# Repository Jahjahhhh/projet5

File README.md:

# Standing desk projet

```/projet5/table-2/```: KiCAD files<br>
```/projet/arduino/projet5```: Arduino files

### Hardware
- 2x 12VDC Linear Actuators (12")
- ESP32 (To access the web and gather info for date, time, weather)
- Dual H-Bridge motor driver (each linear actuator pulls 5 A continuous)
- LED strip (5V Adressable LEDs)
- USB charging hub (2x USB-A & 1x USB-C)
- Ultrasonic sensor to detect when you go from standing to sitting
- MPU6050 (3 axis gyro and accelerometer) to measure the flatness of the table (in case the linear actuators are out of sync)
- 4 Debounced push buttons
- 1 SPDT toggle switch to control linear actuators (ON - OFF - ON)
- 1.8" OLED SPI display

### Schematic

<br>

### PCB

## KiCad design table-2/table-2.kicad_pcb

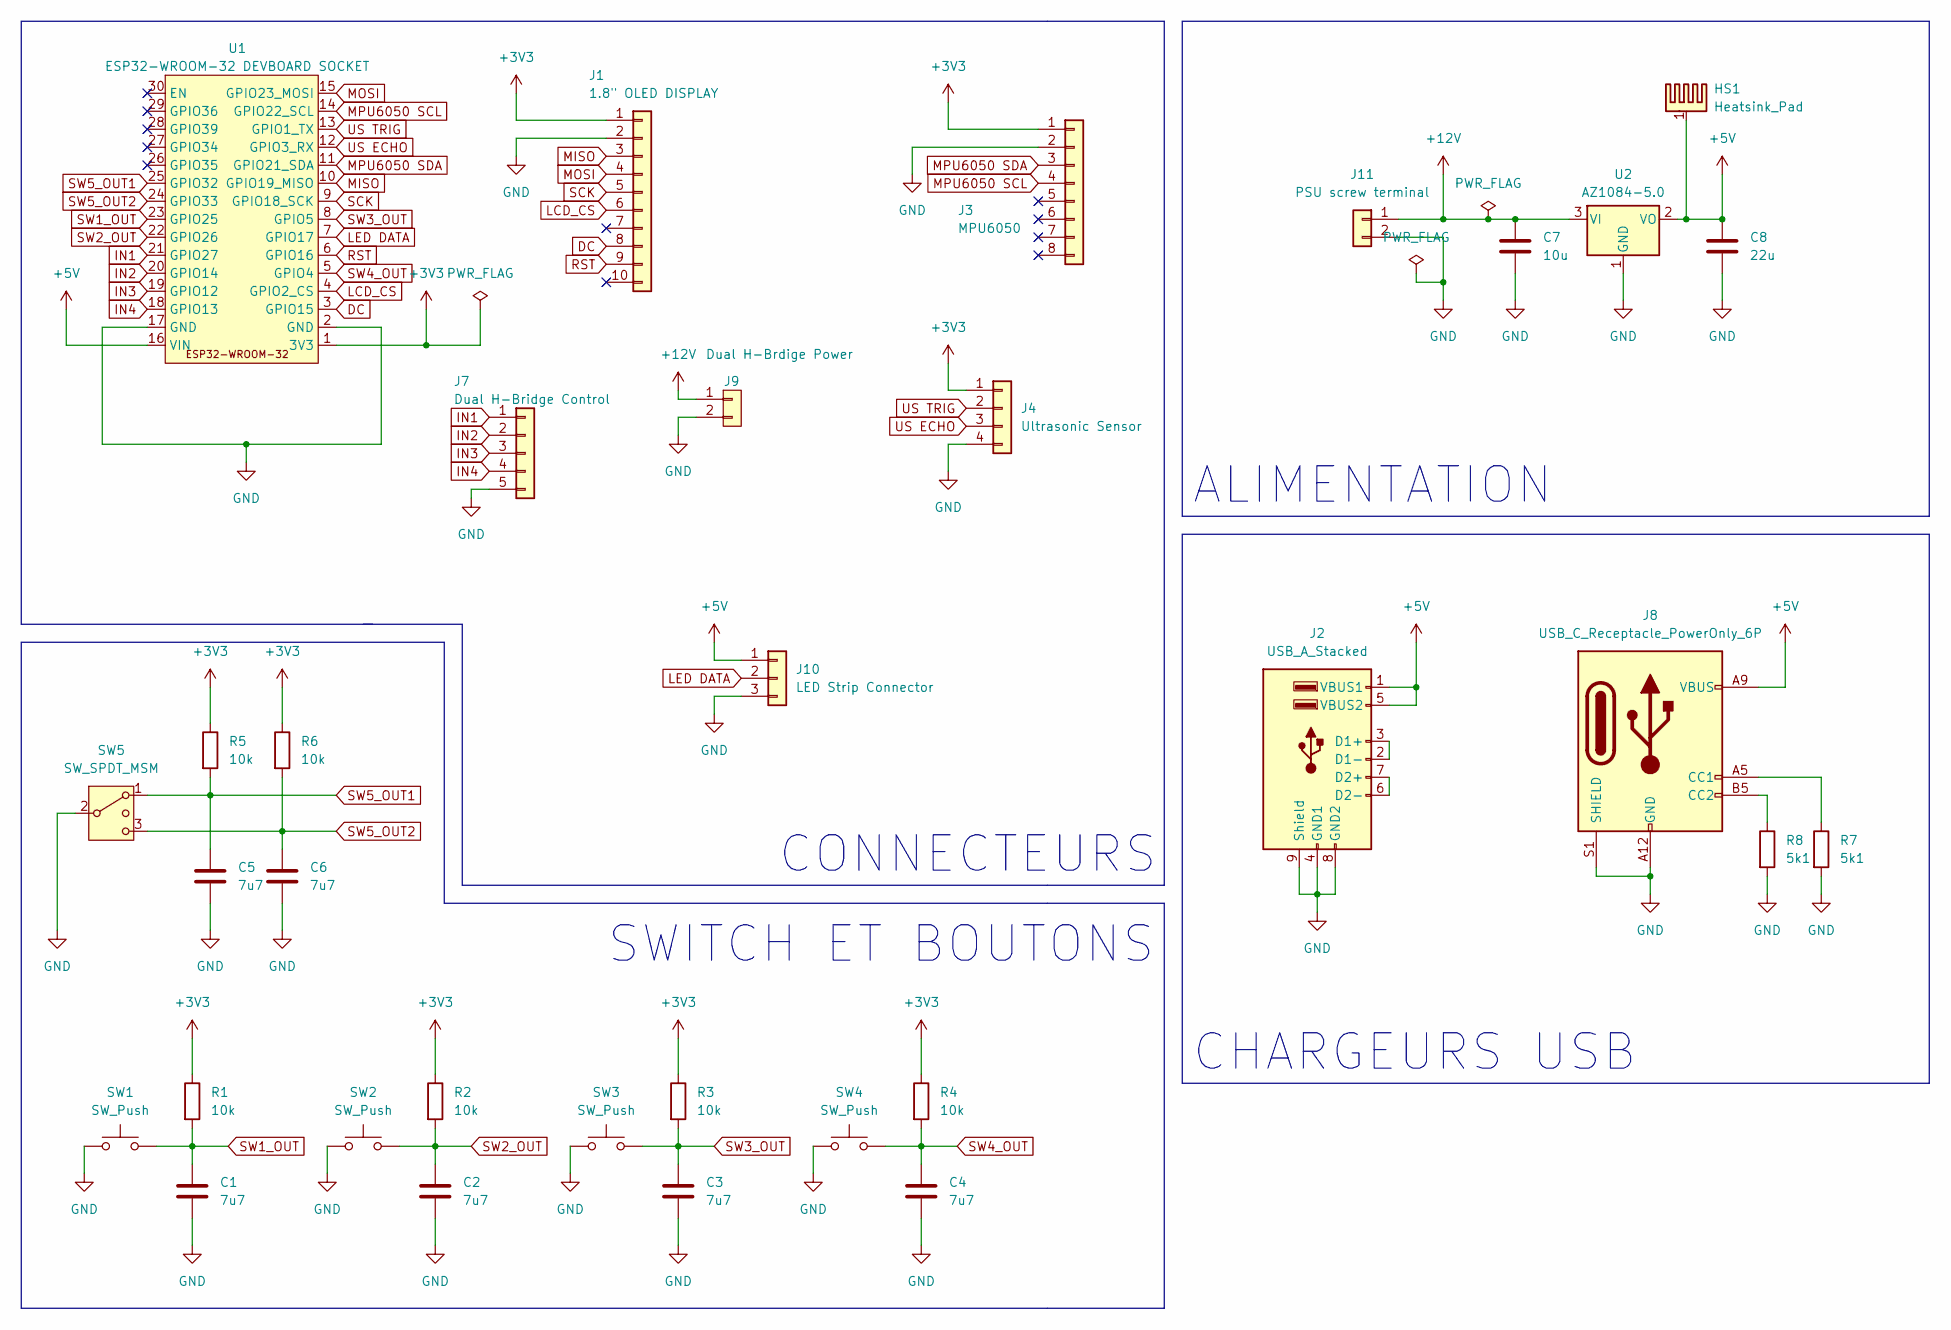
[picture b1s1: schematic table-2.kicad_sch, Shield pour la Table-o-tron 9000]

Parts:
C1, C2, C3, C4, C5, C6: 7u7; C_0805_2012Metric_Pad1.18x1.45mm_HandSolder
C7: 10u; C_0805_2012Metric_Pad1.18x1.45mm_HandSolder
C8: 22u; C_0805_2012Metric_Pad1.18x1.45mm_HandSolder
HS1: Heatsink_Pad; HEATSINK_573100D00000G
J1: 1.8" OLED DISPLAY; PinHeader_1x10_P2.54mm_Vertical
J2: USB_A_Stacked; USB_A_CUI_UJ2-ADH-TH_Horizontal_Stacked
J3: MPU6050; PinHeader_1x08_P2.54mm_Vertical
J4: Ultrasonic Sensor; PinHeader_1x04_P2.54mm_Vertical
J7: Dual H-Bridge Control; PinHeader_1x05_P2.54mm_Vertical
J8: USB_C_Receptacle_PowerOnly_6P; USB_C_Receptacle_GCT_USB4125-xx-x-0190_6P_TopMnt_Horizontal
J9: Dual H-Brdige Power; TerminalBlock_Wuerth_691311400102_P7.62mm; Manufacturer Part Number 0530480260
J10: LED Strip Connector; PinHeader_1x03_P2.54mm_Vertical
J11: PSU screw terminal; TerminalBlock_Wuerth_691311400102_P7.62mm
R1, R2, R3, R4, R5, R6: 10k; R_0805_2012Metric_Pad1.20x1.40mm_HandSolder
R7, R8: 5k1; R_0805_2012Metric_Pad1.20x1.40mm_HandSolder
SW1, SW2, SW3, SW4: SW_Push; Tactile_90_TE
SW5: SW_SPDT_MSM; BST13T1AVR
U1: ESP32-WROOM-32 DEVBOARD SOCKET; ESP32_WROOM_32
U2: AZ1084-5.0; AZ1084CD-5.0TRG1

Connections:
+3V3: J1.1, J3.1, J4.1, R1.1, R2.1, R3.1, R4.1, R5.1, R6.1, U1.1 (3V3)
+5V: C8.1, HS1.1, J2.1 (VBUS1), J2.5 (VBUS2), J8.A9 (VBUS), J8.B9 (VBUS), J10.1, U1.16 (VIN), U2.2 (VO)
+12V: C7.1, J9.1, J11.1, U2.3 (VI)
DC: J1.8, U1.3 (GPIO15)
GND: C1.2, C2.2, C3.2, C4.2, C5.2, C6.2, C7.2, C8.2, J1.2, J2.4 (GND1), J2.8 (GND2), J2.9 (Shield), J3.2, J4.4, J7.5, J8.A12 (GND), J8.B12 (GND), J8.S1 (SHIELD), J9.2, J10.3, J11.2, R7.2, R8.2, SW1.1, SW2.1, SW3.1, SW4.1, SW5.2 (3), U1.2 (GND), U1.17 (GND), U2.1 (GND)
IN1: J7.1, U1.21 (GPIO27)
IN2: J7.2, U1.20 (GPIO14)
IN3: J7.3, U1.19 (GPIO12)
IN4: J7.4, U1.18 (GPIO13)
LCD_CS: J1.6, U1.4 (GPIO2_CS)
LED DATA: J10.2, U1.7 (GPIO17)
MISO: J1.3, U1.10 (GPIO19_MISO)
MOSI: J1.4, U1.15 (GPIO23_MOSI)
MPU6050 SCL: J3.4, U1.14 (GPIO22_SCL)
MPU6050 SDA: J3.3, U1.11 (GPIO21_SDA)
unnamed: J2.2 (D1-), J2.3 (D1+)
unnamed: J2.6 (D2-), J2.7 (D2+)
unnamed: J8.A5 (CC1), R7.1
unnamed: J8.B5 (CC2), R8.1
RST: J1.9, U1.6 (GPIO16)
SCK: J1.5, U1.9 (GPIO18_SCK)
SW1_OUT: C1.1, R1.2, SW1.2, U1.23 (GPIO25)
SW2_OUT: C2.1, R2.2, SW2.2, U1.22 (GPIO26)
SW3_OUT: C3.1, R3.2, SW3.2, U1.8 (GPIO5)
SW4_OUT: C4.1, R4.2, SW4.2, U1.5 (GPIO4)
SW5_OUT1: C5.1, R5.2, SW5.1, U1.25 (GPIO32)
SW5_OUT2: C6.1, R6.2, SW5.3 (4), U1.24 (GPIO33)
US ECHO: J4.3, U1.12 (GPIO3_RX)
US TRIG: J4.2, U1.13 (GPIO1_TX)

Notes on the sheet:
CONNECTEURS
CHARGEURS USB
SWITCH ET BOUTONS
ALIMENTATION

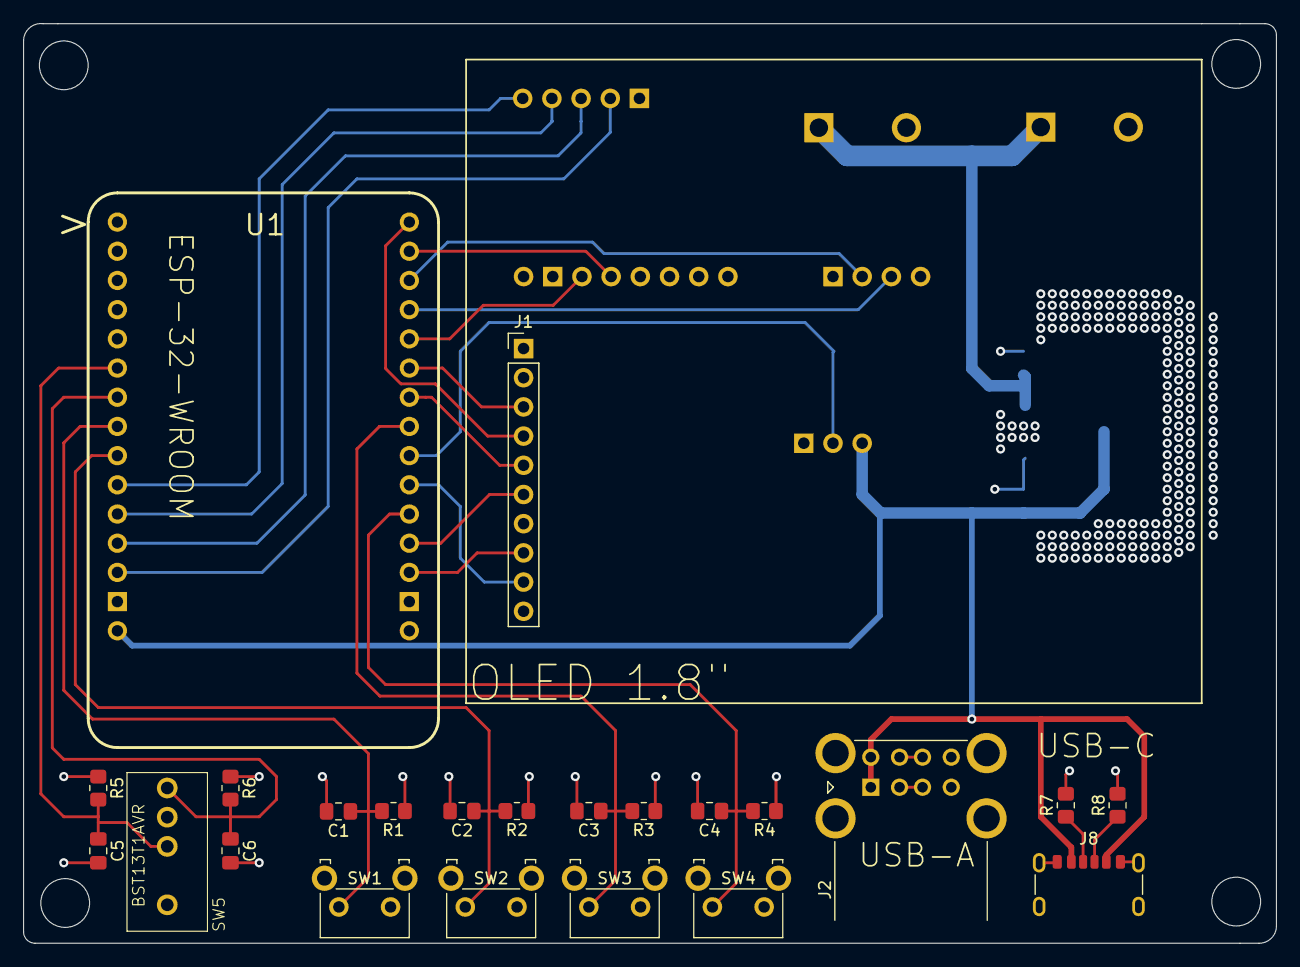
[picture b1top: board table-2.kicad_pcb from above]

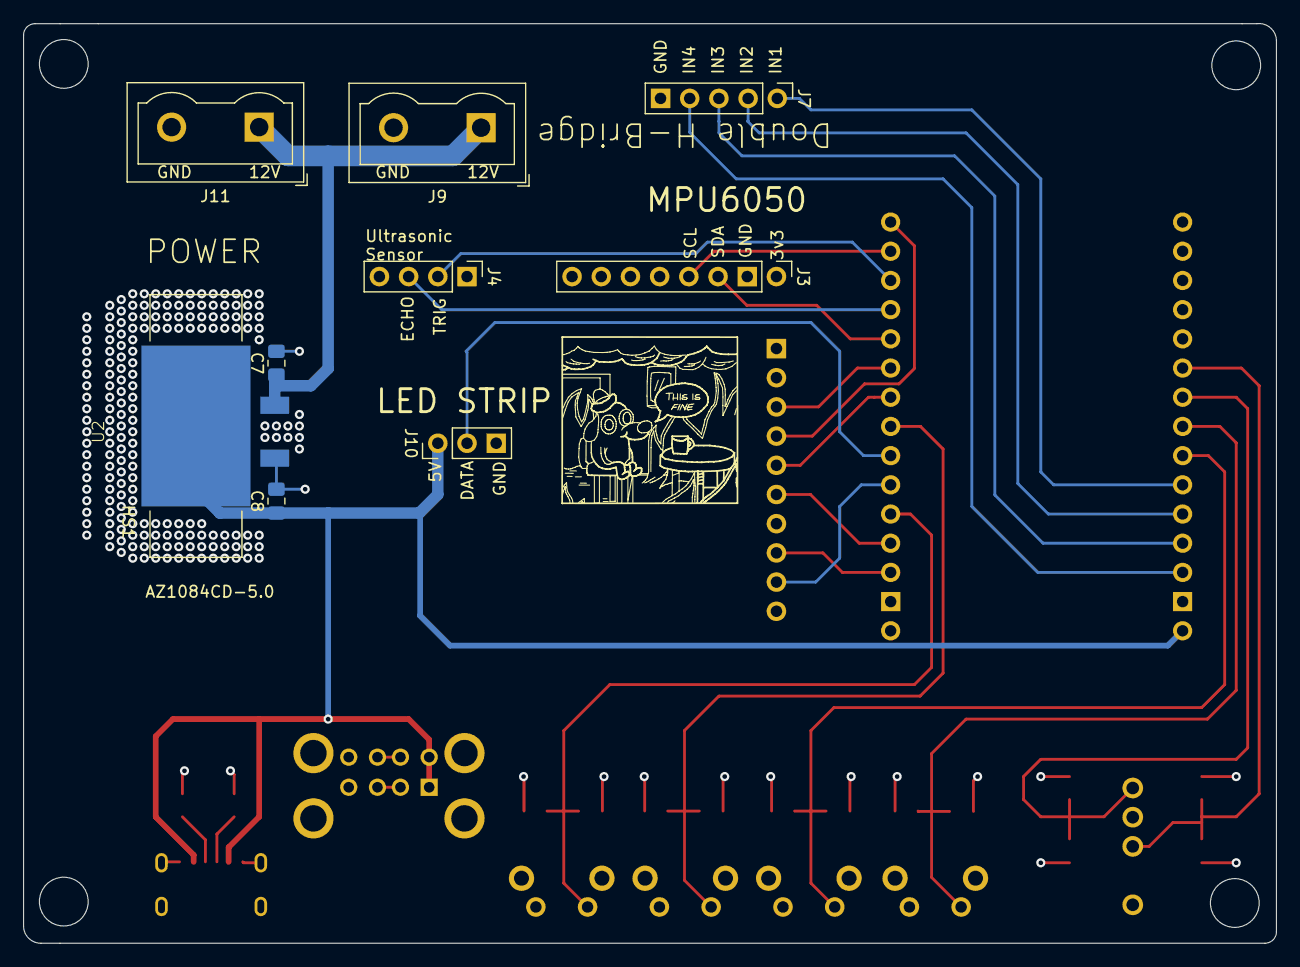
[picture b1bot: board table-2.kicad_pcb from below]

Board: 4 copper layers, 109.0 x 80.0 mm, 33 parts (10 on the bottom side), 29 nets.

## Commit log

2024-10-05 sync
2024-10-05 added an image for the schematic
2024-10-07 added footprints, changed volt reg, changed toggle switch, and more
2024-10-08 updated schematic image
2024-10-08 Update README.md
    changed my toggle switch from a dp3t to a spdt (on/off/on) in the schematic & footprint editor
2024-10-11 pcb v1
2024-10-11 added png of pcb
2024-10-11 updated schematic png
2024-10-14 forgot about the backside of the pcb. this is one much smaller and denser
2024-10-14 updated pcb image
2024-11-10 added basic graphics test for display
2024-12-12 wifi, ntp, weather, rough draft, sync from PC
